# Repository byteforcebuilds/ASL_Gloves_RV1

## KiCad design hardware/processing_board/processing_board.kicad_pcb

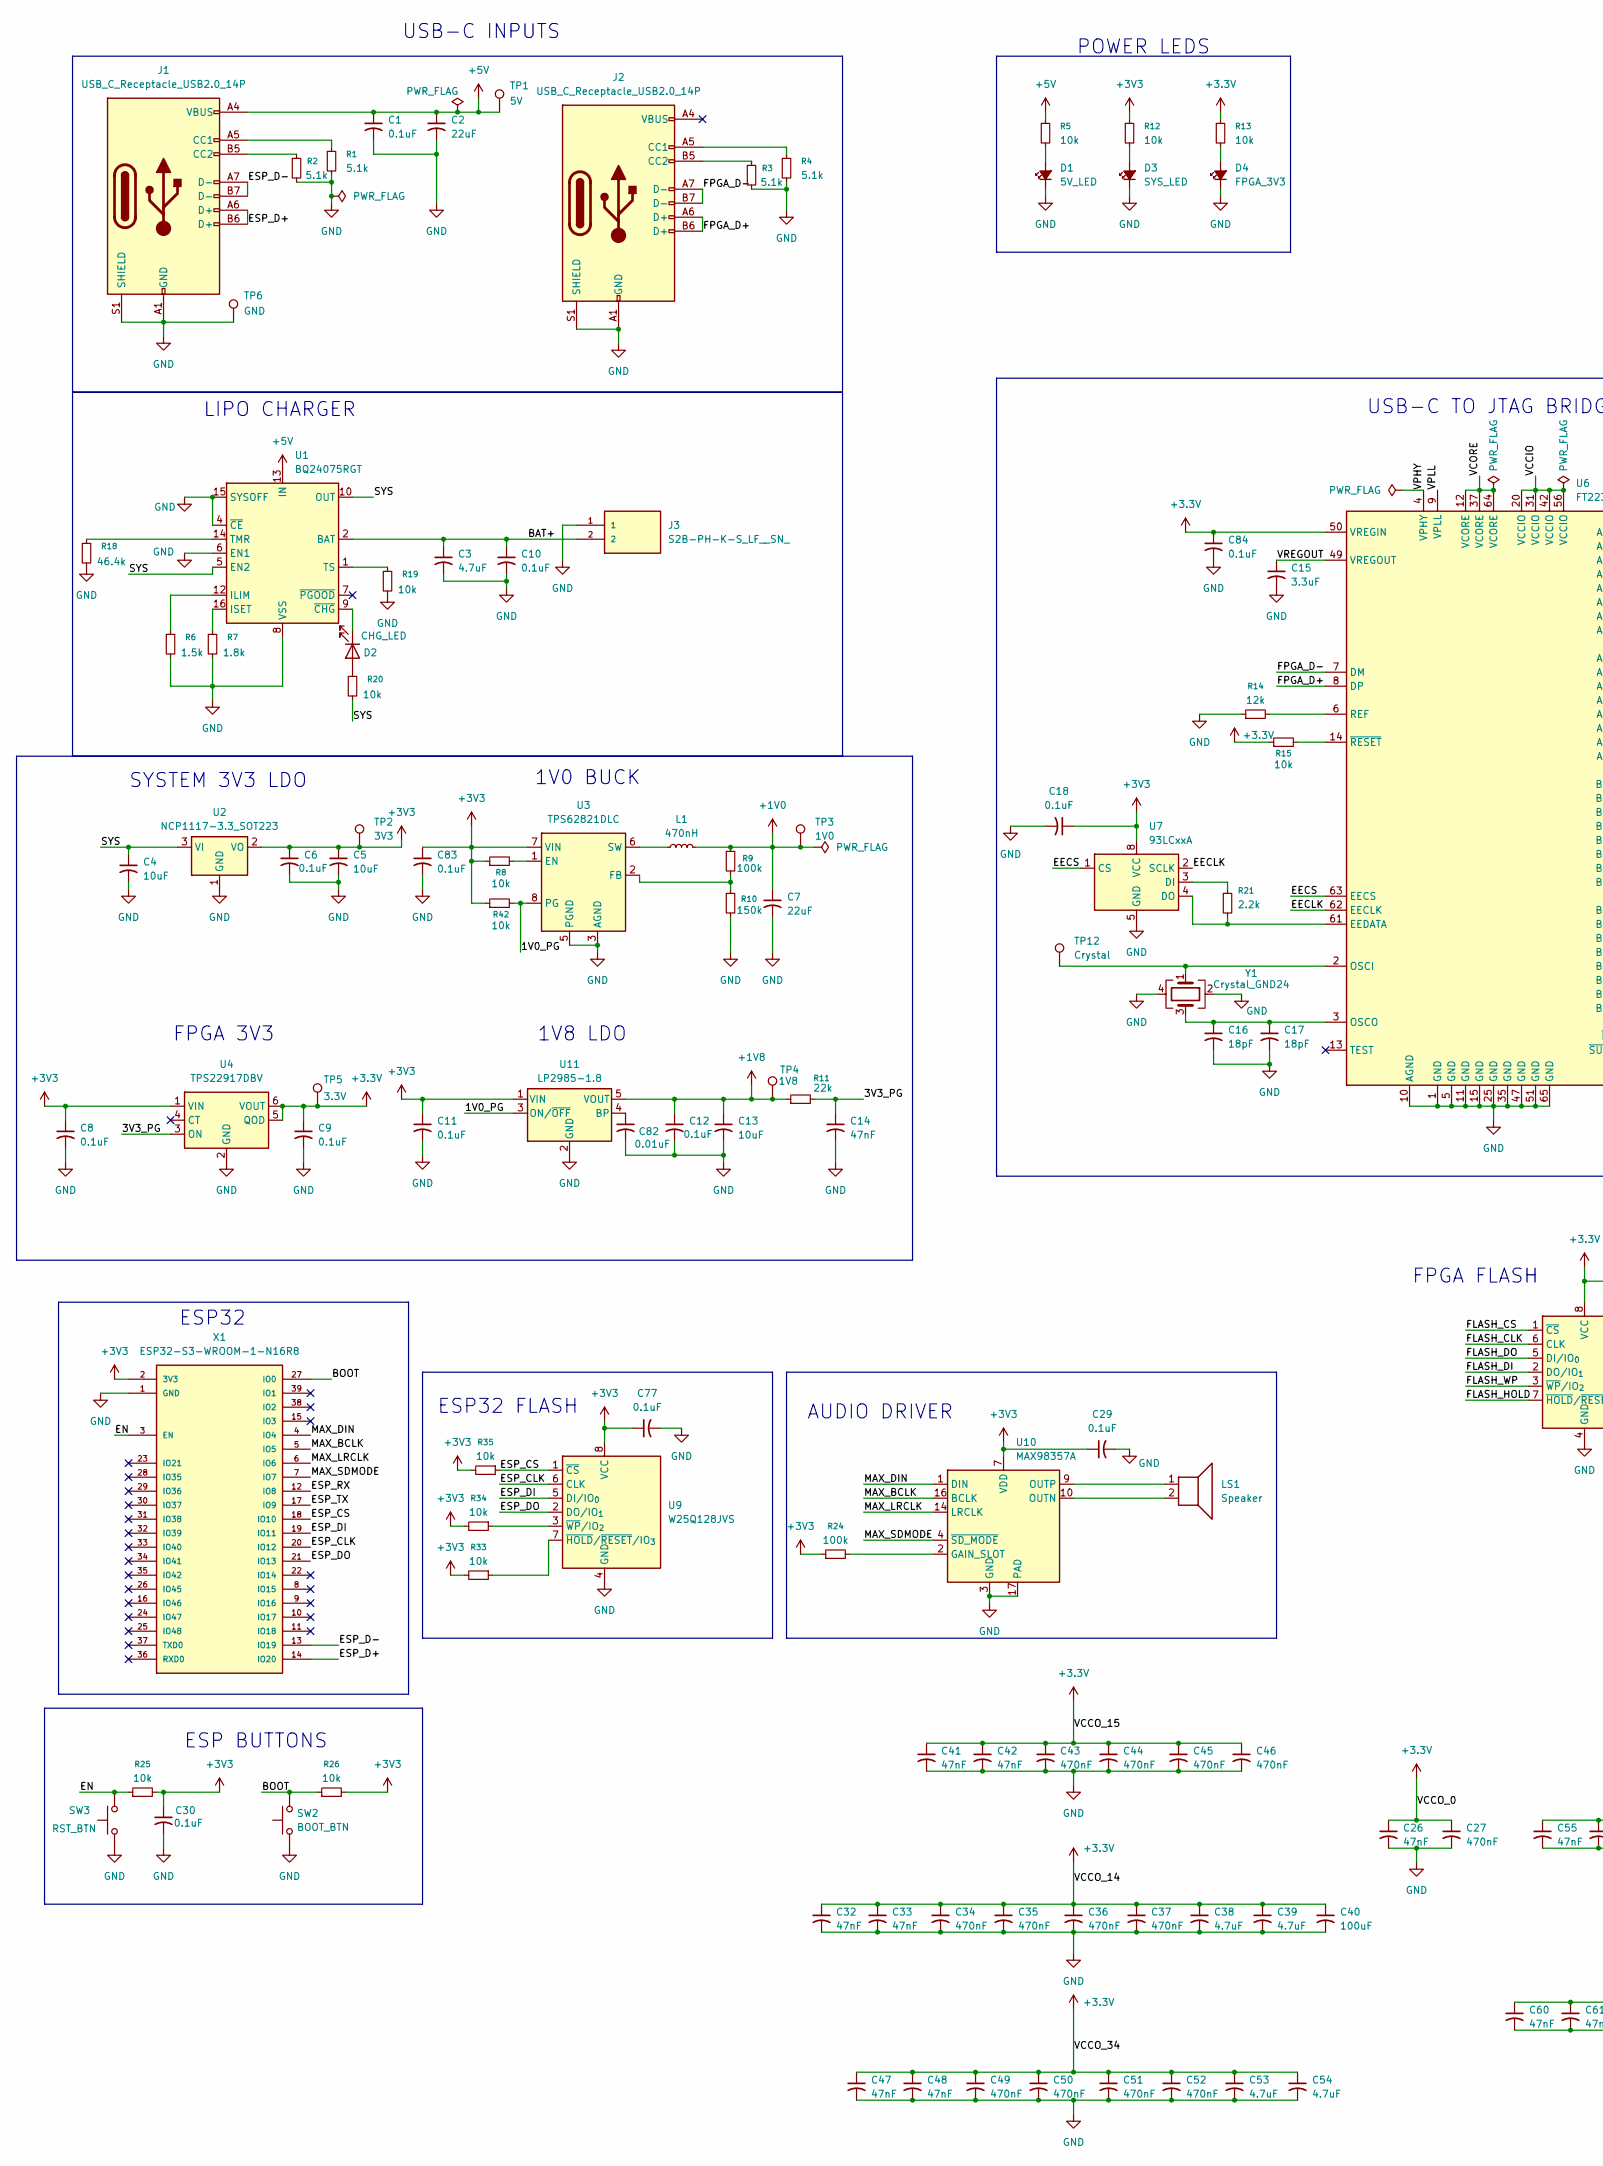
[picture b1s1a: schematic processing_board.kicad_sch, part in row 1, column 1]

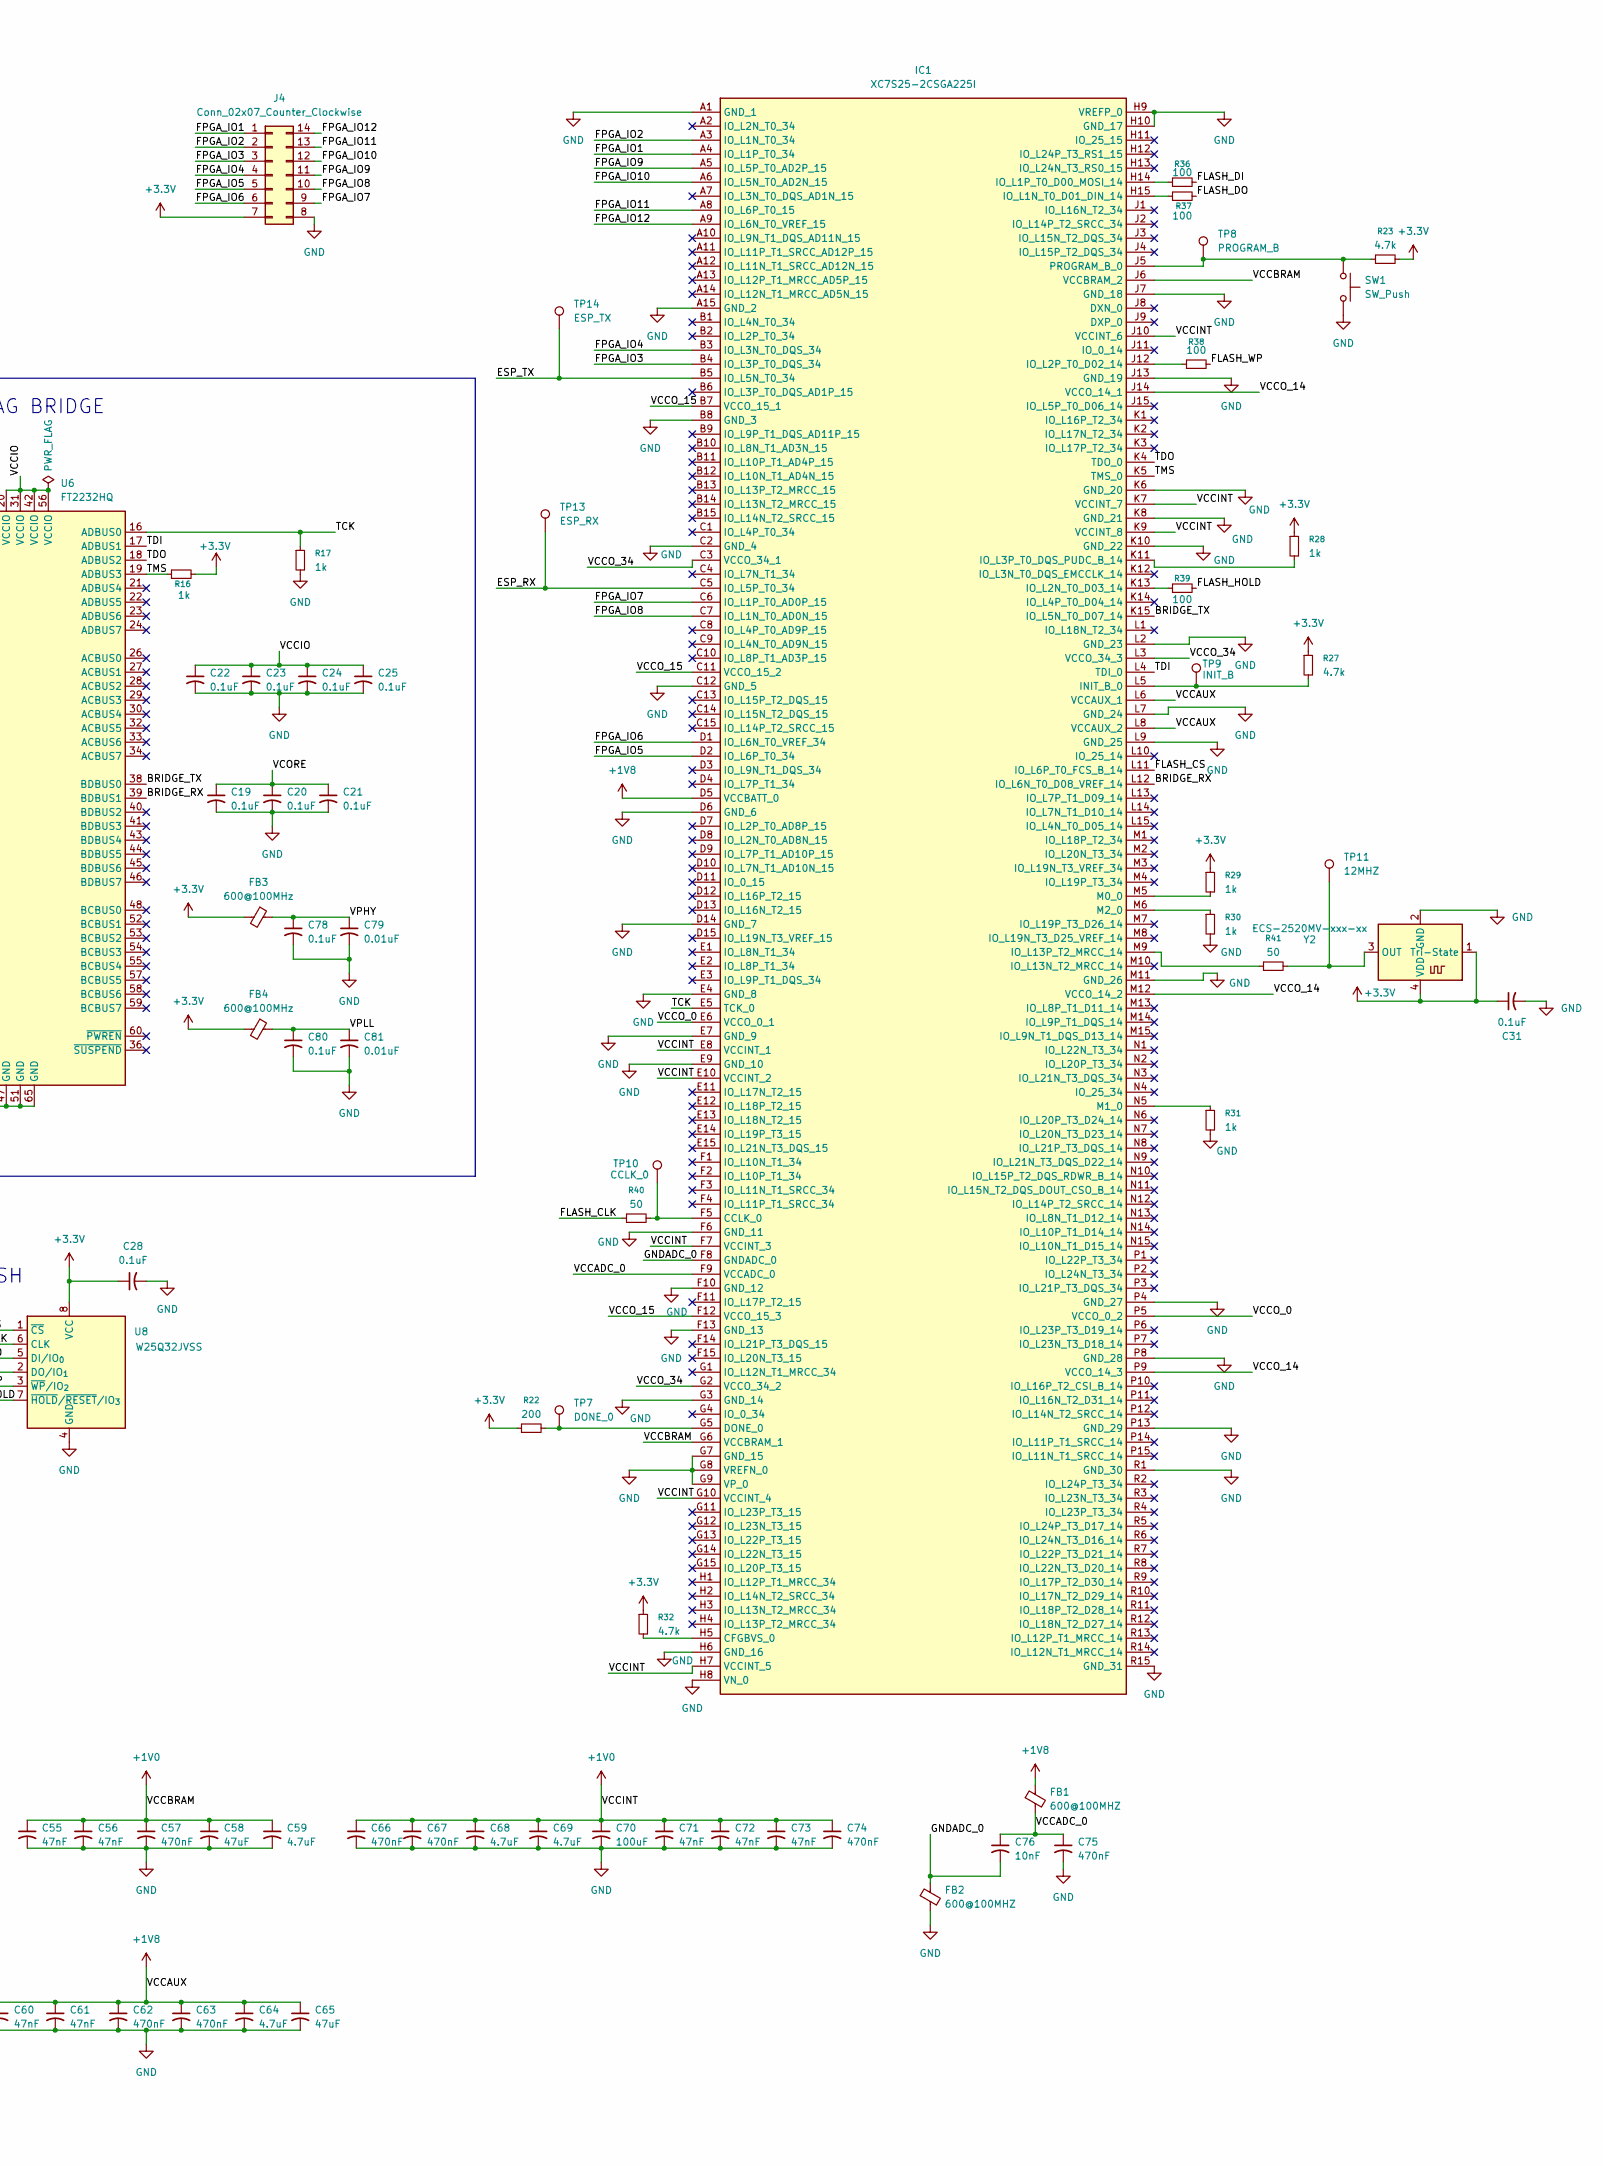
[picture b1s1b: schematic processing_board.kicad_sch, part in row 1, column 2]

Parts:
C1, C6, C8, C9, C11, C12, C18, C19, C20, C21, C22, C23, C24, C25, C28, C29, C30, C31, C77, C78, C80, C83, C84: 0.1uF; C_0402_1005Metric
C2, C7: 22uF; C_0805_2012Metric
C3, C38, C39, C53, C54, C59, C64, C68, C69: 4.7uF; C_0603_1608Metric
C4, C5, C13: 10uF; C_0805_2012Metric
C10: 0.1uF; R_0402_1005Metric
C14: 47nF; C_0805_2012Metric
C15: 3.3uF; C_0603_1608Metric
C16, C17: 18pF; C_0402_1005Metric
C26, C32, C33, C41, C42, C47, C48, C55, C56, C60, C61, C71, C72, C73: 47nF; C_0402_1005Metric
C27, C34, C35, C36, C37, C43, C44, C45, C46, C49, C50, C51, C52, C57, C62, C63, C66, C67, C74, C75: 470nF; C_0402_1005Metric
C40, C70: 100uF; C_0805_2012Metric
C58, C65: 47uF; C_0805_2012Metric
C76: 10nF; C_0402_1005Metric
C79, C81, C82: 0.01uF; C_0402_1005Metric
D1: 5V_LED; LED_0805_2012Metric
D2: CHG_LED; LED_0805_2012Metric
D3: SYS_LED; LED_0805_2012Metric
D4: FPGA_3V3; LED_0805_2012Metric
FB1, FB2: 600@100MHZ; C_0603_1608Metric
FB3, FB4: 600@100MHz; C_0603_1608Metric
IC1: XC7S25-2CSGA225I; BGA225C80P15X15_1300X1300X140; Manufacturer_Part_Number XC7S25-2CSGA225I; Mouser Part Number 217-XC7S25-2CSGA225I
J1, J2: USB_C_Receptacle_USB2.0_14P; USB_C_Receptacle_JAE_DX07S016JA1R1500
J3: S2B-PH-K-S_LF__SN_; JST_S2B-PH-K-S_LF__SN_
J4: Conn_02x07_Counter_Clockwise; PinHeader_2x07_P2.54mm_Vertical
L1: 470nH; INDC2016X120N
LS1: Speaker; JST_PH_S2B-PH-K_1x02_P2.00mm_Horizontal
R1, R2, R3, R4: 5.1k; R_0402_1005Metric
R5, R8, R12, R13, R15, R19, R20, R25, R26, R33, R34, R35, R42: 10k; R_0402_1005Metric
R6: 1.5k; R_0402_1005Metric
R7: 1.8k; R_0402_1005Metric
R9, R24: 100k; R_0402_1005Metric
R10: 150k; R_0402_1005Metric
R11: 22k; R_0402_1005Metric
R14: 12k; R_0402_1005Metric
R16, R17, R28, R29, R30, R31: 1k; R_0402_1005Metric
R18: 46.4k; R_0402_1005Metric
R21: 2.2k; R_0402_1005Metric
R22: 200; R_0402_1005Metric
R23, R27, R32: 4.7k; R_0402_1005Metric
R36, R37, R38, R39: 100; R_0402_1005Metric
R40, R41: 50; R_0402_1005Metric
SW1: SW_Push; SW_SPST_B3U-1000P
SW2: BOOT_BTN; SW_SPST_B3U-1000P
SW3: RST_BTN; SW_SPST_B3U-1000P
TP1: 5V; TestPoint_Loop_D2.60mm_Drill0.9mm_Beaded
TP2: 3V3; TestPoint_Loop_D2.60mm_Drill0.9mm_Beaded
TP3: 1V0; TestPoint_Loop_D2.60mm_Drill0.9mm_Beaded
TP4: 1V8; TestPoint_Loop_D2.60mm_Drill0.9mm_Beaded
TP5: 3.3V; TestPoint_Loop_D2.60mm_Drill0.9mm_Beaded
TP6: GND; TestPoint_Loop_D2.60mm_Drill0.9mm_Beaded
TP7: DONE_0; TestPoint_Loop_D2.60mm_Drill0.9mm_Beaded
TP8: PROGRAM_B; TestPoint_Loop_D2.60mm_Drill0.9mm_Beaded
TP9: INIT_B; TestPoint_Loop_D2.60mm_Drill0.9mm_Beaded
TP10: CCLK_0; TestPoint_Loop_D2.60mm_Drill0.9mm_Beaded
TP11: 12MHZ; TestPoint_Loop_D2.60mm_Drill0.9mm_Beaded
TP12: Crystal; TestPoint_Loop_D2.60mm_Drill0.9mm_Beaded
TP13: ESP_RX; TestPoint_Loop_D2.60mm_Drill0.9mm_Beaded
TP14: ESP_TX; TestPoint_Loop_D2.60mm_Drill0.9mm_Beaded
U1: BQ24075RGT; VQFN-16-1EP_3x3mm_P0.5mm_EP1.6x1.6mm
U2: NCP1117-3.3_SOT223; SOT-223-3_TabPin2
U3: TPS62821DLC; Texas_VSON-HR-8_1.5x2mm_P0.5mm
U4: TPS22917DBV; SOT-23-6
U6: FT2232HQ; QFN-64-1EP_9x9mm_P0.5mm_EP4.35x4.35mm
U7: 93LCxxA; SOIC-8_3.9x4.9mm_P1.27mm
U8: W25Q32JVSS; SOIC-8_5.3x5.3mm_P1.27mm
U9: W25Q128JVS; SOIC-8_5.3x5.3mm_P1.27mm
U10: MAX98357A; TQFN-16-1EP_3x3mm_P0.5mm_EP1.23x1.23mm
U11: LP2985-1.8; SOT-23-5
X1: ESP32-S3-WROOM-1-N16R8; ESP32S3WROOM1N8R2; MANUFACTURER_PART_NUMBER ESP32-S3-WROOM-1-N16R8
Y1: Crystal_GND24; Crystal_SMD_3225-4Pin_3.2x2.5mm
Y2: ECS-2520MV-xxx-xx; Oscillator_SMD_ECS_2520MV-xxx-xx-4Pin_2.5x2.0mm

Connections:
+1V0: C7.1, C55.1, C56.1, C57.1, C58.1, C59.1, C66.1, C67.1, C68.1, C69.1, C70.1, C71.1, C72.1, C73.1, C74.1, IC1.E8 (VCCINT_1), IC1.E10 (VCCINT_2), IC1.F7 (VCCINT_3), IC1.G6 (VCCBRAM_1), IC1.G10 (VCCINT_4), IC1.H7 (VCCINT_5), IC1.J6 (VCCBRAM_2), IC1.J10 (VCCINT_6), IC1.K7 (VCCINT_7), IC1.K9 (VCCINT_8), L1.2, R9.1, TP3.1
+1V8: C12.1, C13.1, C60.1, C61.1, C62.1, C63.1, C64.1, C65.1, FB1.1, IC1.D5 (VCCBATT_0), IC1.L6 (VCCAUX_1), IC1.L8 (VCCAUX_2), R11.1, TP4.1, U11.5 (VOUT)
+3.3V: C9.1, C26.1, C27.1, C28.1, C31.1, C32.1, C33.1, C34.1, C35.1, C36.1, C37.1, C38.1, C39.1, C40.1, C41.1, C42.1, C43.1, C44.1, C45.1, C46.1, C47.1, C48.1, C49.1, C50.1, C51.1, C52.1, C53.1, C54.1, C84.1, FB3.2, FB4.2, IC1.B7 (VCCO_15_1), IC1.C3 (VCCO_34_1), IC1.C11 (VCCO_15_2), IC1.E6 (VCCO_0_1), IC1.F12 (VCCO_15_3), IC1.G2 (VCCO_34_2), IC1.J14 (VCCO_14_1), IC1.L3 (VCCO_34_3), IC1.M12 (VCCO_14_2), IC1.P5 (VCCO_0_2), IC1.P9 (VCCO_14_3), J4.7, R13.1, R15.1, R16.2, R22.1, R23.2, R27.1, R28.1, R29.1, R32.1, TP5.1, U4.5 (QOD), U4.6 (VOUT), U6.50 (VREGIN), U8.8 (VCC), Y2.1 (Tri-State), Y2.4 (VDD)
+3V3: C5.1, C6.1, C8.1, C11.1, C18.1, C29.1, C30.1, C77.1, C83.1, R8.1, R12.1, R24.1, R25.2, R26.2, R33.2, R34.2, R35.2, R42.1, TP2.1, U2.2 (VO), U3.7 (VIN), U4.1 (VIN), U7.8 (VCC), U9.8 (VCC), U10.7 (VDD), U10.8 (VDD), U11.1 (VIN), X1.2 (3V3)
+5V: C1.1, C2.1, J1.A4 (VBUS), J1.A9 (VBUS), J1.B4 (VBUS), J1.B9 (VBUS), R5.1, TP1.1, U1.13 (IN)
/1V0_PG: R42.2, U3.8 (PG), U11.3 (ON/~OFF)
/3V3_PG: C14.1, R11.2, U4.3 (ON)
/<NO NET>: C3.1, C10.1, J3.2, U1.2 (BAT), U1.3 (BAT)
/BOOT: R26.1, SW2.2, X1.27 (IO0)
/BRIDGE_RX: IC1.L12 (IO_L6N_T0_D08_VREF_14), U6.39 (BDBUS1)
/BRIDGE_TX: IC1.K15 (IO_L5N_T0_D07_14), U6.38 (BDBUS0)
/EECLK: U6.62 (EECLK), U7.2 (SCLK)
/EECS: U6.63 (EECS), U7.1 (CS)
/EN: R25.1, SW3.2, X1.3 (EN)
/ESP_CLK: U9.6 (CLK), X1.20 (IO12)
/ESP_CS: R35.1, U9.1 (~CS), X1.18 (IO10)
/ESP_D+: J1.A6 (D+), J1.B6 (D+), X1.14 (IO20)
/ESP_D-: J1.A7 (D-), J1.B7 (D-), X1.13 (IO19)
/ESP_DI: U9.5 (DI/IO_{0}), X1.19 (IO11)
/ESP_DO: U9.2 (DO/IO_{1}), X1.21 (IO13)
/ESP_RX: IC1.C5 (IO_L5P_T0_34), TP13.1, X1.12 (IO8)
/ESP_TX: IC1.B5 (IO_L5N_T0_34), TP14.1, X1.17 (IO9)
/FLASH_CLK: R40.1, U8.6 (CLK)
/FLASH_CS: IC1.L11 (IO_L6P_T0_FCS_B_14), U8.1 (~CS)
/FLASH_DI: R36.2, U8.2 (DO/IO_{1})
/FLASH_DO: R37.2, U8.5 (DI/IO_{0})
/FLASH_HOLD: R39.2, U8.7 (~HOLD/~RESET/IO_{3})
/FLASH_WP: R38.2, U8.3 (~WP/IO_{2})
/FPGA_D+: J2.A6 (D+), J2.B6 (D+), U6.8 (DP)
/FPGA_D-: J2.A7 (D-), J2.B7 (D-), U6.7 (DM)
/FPGA_IO1: IC1.A4 (IO_L1P_T0_34), J4.1
/FPGA_IO2: IC1.A3 (IO_L1N_T0_34), J4.2
/FPGA_IO3: IC1.B4 (IO_L3P_T0_DQS_34), J4.3
/FPGA_IO4: IC1.B3 (IO_L3N_T0_DQS_34), J4.4
/FPGA_IO5: IC1.D2 (IO_L6P_T0_34), J4.5
/FPGA_IO6: IC1.D1 (IO_L6N_T0_VREF_34), J4.6
/FPGA_IO7: IC1.C6 (IO_L1P_T0_AD0P_15), J4.9
/FPGA_IO8: IC1.C7 (IO_L1N_T0_AD0N_15), J4.10
/FPGA_IO9: IC1.A5 (IO_L5P_T0_AD2P_15), J4.11
/FPGA_IO10: IC1.A6 (IO_L5N_T0_AD2N_15), J4.12
/FPGA_IO11: IC1.A8 (IO_L6P_T0_15), J4.13
/FPGA_IO12: IC1.A9 (IO_L6N_T0_VREF_15), J4.14
/GNDADC_0: C76.2, FB2.1, IC1.F8 (GNDADC_0)
/MAX_BCLK: U10.16 (BCLK), X1.5 (IO5)
/MAX_DIN: U10.1 (DIN), X1.4 (IO4)
/MAX_LRCLK: U10.14 (LRCLK), X1.6 (IO6)
/MAX_SDMODE: U10.4 (~SD_MODE), X1.7 (IO7)
/SYS: C4.1, R20.2, U1.5 (EN2), U1.10 (OUT), U1.11 (OUT), U2.3 (VI)
/TCK: IC1.E5 (TCK_0), R17.1, U6.16 (ADBUS0)
/TDI: IC1.L4 (TDI_0), U6.17 (ADBUS1)
/TDO: IC1.K4 (TDO_0), U6.18 (ADBUS2)
/TMS: IC1.K5 (TMS_0), R16.1, U6.19 (ADBUS3)
/VCCADC_0: C75.1, C76.1, FB1.2, IC1.F9 (VCCADC_0)
/VCCIO: C22.1, C23.1, C24.1, C25.1, U6.20 (VCCIO), U6.31 (VCCIO), U6.42 (VCCIO), U6.56 (VCCIO)
/VCORE: C19.1, C20.1, C21.1, U6.12 (VCORE), U6.37 (VCORE), U6.64 (VCORE)
/VPHY: C78.1, C79.1, FB3.1, U6.4 (VPHY)
/VPLL: C80.1, C81.1, FB4.1, U6.9 (VPLL)
/VREGOUT: C15.1, U6.49 (VREGOUT)
GND: C1.2, C2.2, C3.2, C4.2, C5.2, C6.2, C7.2, C8.2, C9.2, C10.2, C11.2, C12.2, C13.2, C14.2, C15.2, C16.2, C17.2, C18.2, C19.2, C20.2, C21.2, C22.2, C23.2, C24.2, C25.2, C26.2, C27.2, C28.2, C29.2, C30.2, C31.2, C32.2, C33.2, C34.2, C35.2, C36.2, C37.2, C38.2, C39.2, C40.2, C41.2, C42.2, C43.2, C44.2, C45.2, C46.2, C47.2, C48.2, C49.2, C50.2, C51.2, C52.2, C53.2, C54.2, C55.2, C56.2, C57.2, C58.2, C59.2, C60.2, C61.2, C62.2, C63.2, C64.2, C65.2, C66.2, C67.2, C68.2, C69.2, C70.2, C71.2, C72.2, C73.2, C74.2, C75.2, C77.2, C78.2, C79.2, C80.2, C81.2, C82.2, C83.2, C84.2, D1.1 (K), D3.1 (K), D4.1 (K), FB2.2, IC1.A1 (GND_1), IC1.A15 (GND_2), IC1.B8 (GND_3), IC1.C2 (GND_4), IC1.C12 (GND_5), IC1.D6 (GND_6), IC1.D14 (GND_7), IC1.E4 (GND_8), IC1.E7 (GND_9), IC1.E9 (GND_10), IC1.F6 (GND_11), IC1.F10 (GND_12), IC1.F13 (GND_13), IC1.G3 (GND_14), IC1.G7 (GND_15), IC1.G8 (VREFN_0), IC1.G9 (VP_0), IC1.H6 (GND_16), IC1.H8 (VN_0), IC1.H9 (VREFP_0), IC1.H10 (GND_17), IC1.J7 (GND_18), IC1.J13 (GND_19), IC1.K6 (GND_20), IC1.K8 (GND_21), IC1.K10 (GND_22), IC1.L2 (GND_23), IC1.L7 (GND_24), IC1.L9 (GND_25), IC1.M11 (GND_26), IC1.P4 (GND_27), IC1.P8 (GND_28), IC1.P13 (GND_29), IC1.R1 (GND_30), IC1.R15 (GND_31), J1.A1 (GND), J1.A12 (GND), J1.B1 (GND), J1.B12 (GND), J1.S1 (SHIELD), J2.A1 (GND), J2.A12 (GND), J2.B1 (GND), J2.B12 (GND), J2.S1 (SHIELD), J3.1, J4.8, R1.2, R2.2, R3.2, R4.2, R6.2, R7.2, R10.2, R14.1, R17.2, R18.2, R19.2, R30.2, R31.2, SW1.2, SW2.1, SW3.1, TP6.1, U1.4 (~CE), U1.6 (EN1), U1.8 (VSS), U1.15 (SYSOFF), U1.17 (VSS), U2.1 (GND), U3.3 (AGND), U3.5 (PGND), U4.2 (GND), U6.1 (GND), U6.5 (GND), U6.10 (AGND), U6.11 (GND), U6.15 (GND), U6.25 (GND), U6.35 (GND), U6.47 (GND), U6.51 (GND), U6.65 (GND), U7.5 (GND), U8.4 (GND), U9.4 (GND), U10.3 (GND), U10.11 (GND), U10.15 (GND), U10.17 (PAD), U11.2 (GND), X1.1 (GND), X1.40 (GND), X1.41 (GND), X1.42 (GND), X1.43 (GND), X1.44 (GND), X1.45 (GND), X1.46 (GND), X1.47 (GND), X1.48 (GND), X1.49 (GND), Y1.2, Y1.4, Y2.2 (GND)
unnamed: D1.2 (A), R5.2
unnamed: D2.2 (A), R20.1
unnamed: D2.1 (K), U1.9 (~CHG)
unnamed: D3.2 (A), R12.2
unnamed: D4.2 (A), R13.2
unnamed: IC1.F5 (CCLK_0), R40.2, TP10.1
unnamed: IC1.H5 (CFGBVS_0), R32.2
unnamed: IC1.G5 (DONE_0), R22.2, TP7.1
unnamed: IC1.L5 (INIT_B_0), R27.2, TP9.1
unnamed: IC1.H15 (IO_L1N_T0_D01_DIN_14), R37.1
unnamed: IC1.H14 (IO_L1P_T0_D00_MOSI_14), R36.1
unnamed: IC1.K13 (IO_L2N_T0_D03_14), R39.1
unnamed: IC1.J12 (IO_L2P_T0_D02_14), R38.1
unnamed: IC1.K11 (IO_L3P_T0_DQS_PUDC_B_14), R28.2
unnamed: IC1.M9 (IO_L13P_T2_MRCC_14), R41.1
unnamed: IC1.M5 (M0_0), R29.2
unnamed: IC1.N5 (M1_0), R31.1
unnamed: IC1.M6 (M2_0), R30.1
unnamed: IC1.J5 (PROGRAM_B_0), R23.1, SW1.1, TP8.1
unnamed: J1.A5 (CC1), R1.1
unnamed: J1.B5 (CC2), R2.1
unnamed: J2.A5 (CC1), R4.1
unnamed: J2.B5 (CC2), R3.1
unnamed: R6.1, U1.12 (ILIM)
unnamed: R7.1, U1.16 (ISET)
unnamed: R18.1, U1.14 (TMR)
unnamed: R19.1, U1.1 (TS)
unnamed: R8.2, U3.1 (EN)
unnamed: R9.2, R10.1, U3.2 (FB)
unnamed: L1.1, U3.6 (SW)
unnamed: R21.2, U6.61 (EEDATA), U7.4 (DO)
unnamed: TP12.1, U6.2 (OSCI), Y1.1
unnamed: C16.1, C17.1, U6.3 (OSCO), Y1.3
unnamed: R14.2, U6.6 (REF)
unnamed: R15.2, U6.14 (~RESET)
unnamed: R21.1, U7.3 (DI)
unnamed: R33.1, U9.7 (~HOLD/~RESET/IO_{3})
unnamed: R34.1, U9.3 (~WP/IO_{2})
unnamed: R24.2, U10.2 (GAIN_SLOT)
unnamed: C82.1, U11.4 (BP)
unnamed: R41.2, TP11.1, Y2.3 (OUT)

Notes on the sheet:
1V0 BUCK
ESP BUTTONS
LIPO CHARGER
SYSTEM 3V3 LDO
FPGA FLASH
POWER LEDS
FPGA 3V3
USB-C INPUTS
1V8 LDO
USB-C TO JTAG BRIDGE
AUDIO DRIVER
ESP32
ESP32 FLASH

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
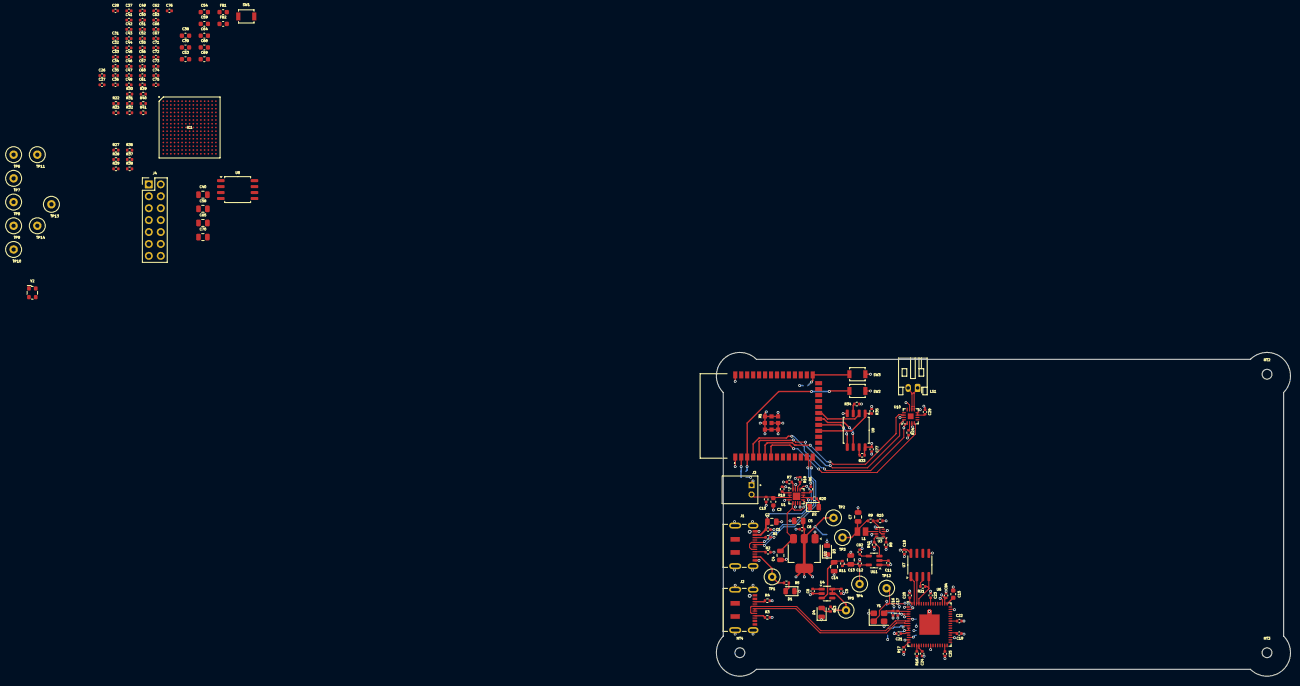
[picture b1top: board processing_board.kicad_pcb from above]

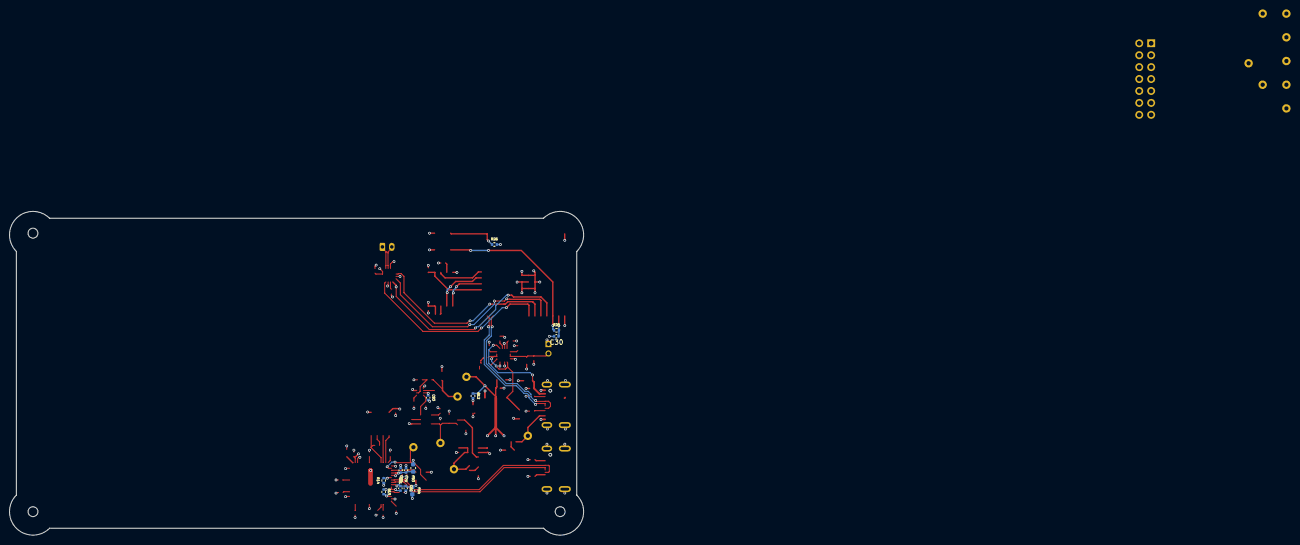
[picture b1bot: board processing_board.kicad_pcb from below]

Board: 4 copper layers, 122.3 x 69.0 mm, 174 parts (13 on the bottom side), 100 nets.

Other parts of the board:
MT2, MT3, MT4: MountingHole_2.1mm

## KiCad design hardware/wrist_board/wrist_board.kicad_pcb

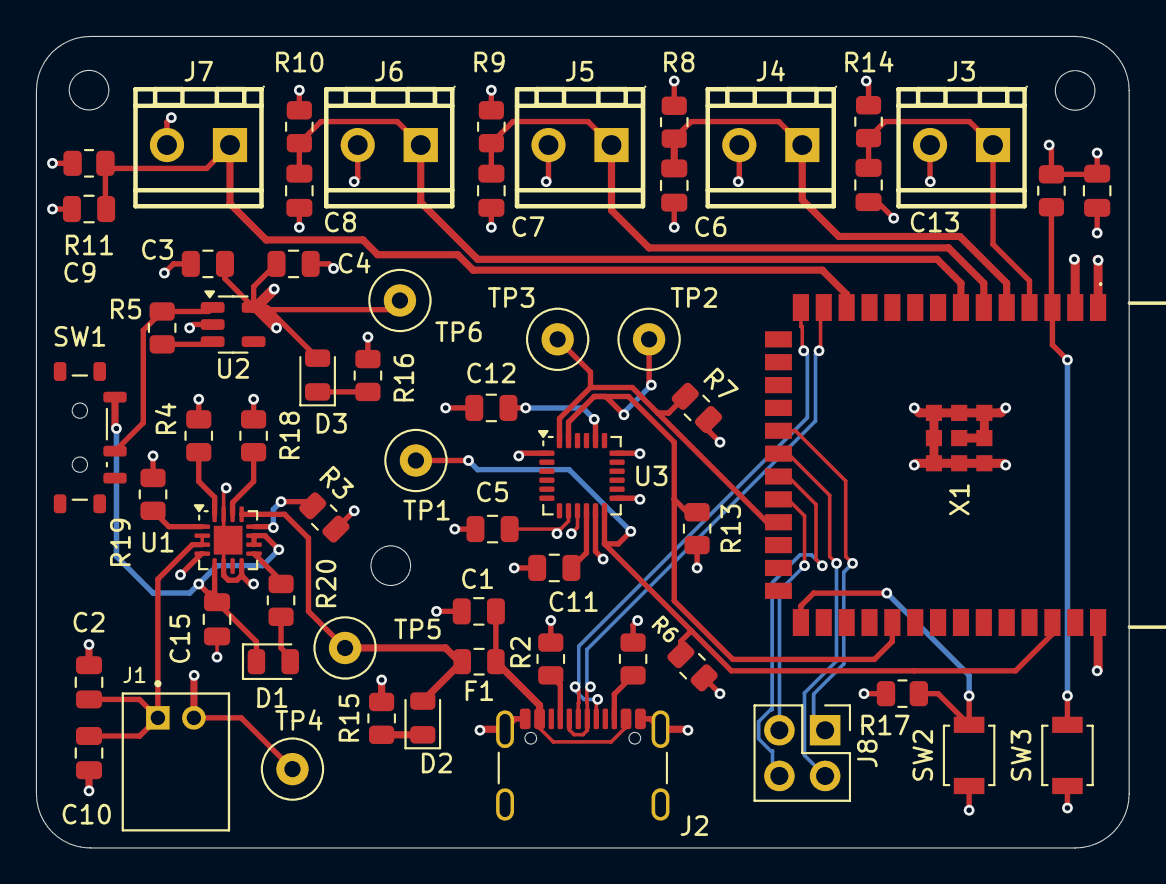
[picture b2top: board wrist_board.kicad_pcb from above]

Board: 4 copper layers, 60.7 x 45.1 mm, 60 parts (0 on the bottom side), 36 nets.

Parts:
C1, C3, C15: 10uF; C_0805_2012Metric
C2: 4.7uF; C_0805_2012Metric
C4, C5, C6, C7, C8, C9, C10, C11, C13, C14: 0.1uF; C_0805_2012Metric
C12: 2.2nF; C_0805_2012Metric
D1: CHG_LED; LED_0805_2012Metric
D2: 5V_LED; LED_0805_2012Metric
D3: 3V3_LED; LED_0805_2012Metric
F1: Polyfuse; Fuse_0805_2012Metric
J1: S2B-PH-K-S_LF__SN_; JST_S2B-PH-K-S_LF__SN_
J2: USB_C_Receptacle_USB2.0_14P; USB_C_Receptacle_GCT_USB4105-xx-A_16P_TopMnt_Horizontal
J3, J4, J5, J6, J7: Conn_01x02; CONN-TH_DG350-3.5-02P-14-00A-H
J8: GPIOs; PinHeader_2x02_P2.54mm_Vertical
R1, R2: 5.1k; R_0805_2012Metric
R3: 1.5k; R_0805_2012Metric
R4: 1.8k; R_0805_2012Metric
R5, R12, R17, R19: 10k; R_0805_2012Metric
R6, R7, R13: 4.7k; R_0805_2012Metric
R8, R9, R10, R11, R14: 22k; R_0805_2012Metric
R15, R16, R20: 1k; R_0805_2012Metric
R18: 46.4k; R_0805_2012Metric
SW1: SW_SPST; SW_SPDT_Shouhan_MSK12C02
SW2: BOOT_BTN; SW_SPST_B3U-1000P
SW3: RST_BTN; SW_SPST_B3U-1000P
TP1: INT_TP; TestPoint_Loop_D2.60mm_Drill0.9mm_Beaded
TP2: SCL_TP; TestPoint_Loop_D2.60mm_Drill0.9mm_Beaded
TP3: SDA_TP; TestPoint_Loop_D2.60mm_Drill0.9mm_Beaded
TP4: GND_TP; TestPoint_Loop_D2.60mm_Drill0.9mm_Beaded
TP5: 5V_TP; TestPoint_Loop_D2.60mm_Drill0.9mm_Beaded
TP6: 3V3_TP; TestPoint_Loop_D2.60mm_Drill0.9mm_Beaded
U1: BQ24075RGT; VQFN-16-1EP_3x3mm_P0.5mm_EP1.6x1.6mm
U2: TLV75533PDBV; SOT-23-5
U3: MPU-6050; InvenSense_QFN-24_4x4mm_P0.5mm
X1: ESP32-S3-WROOM-1-N16R8; ESP32S3WROOM1N8R2

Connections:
+3V3: C3.1, C4.1, C5.1, C14.1, D3.2 (A), R6.1, R7.1, R8.2, R9.2, R10.2, R11.2, R12.2, R13.1, R14.2, R17.2, TP6.1, U2.5 (OUT), U3.8 (VLOGIC), U3.13 (VDD), X1.2 (3V3)
+5V: D2.2 (A), F1.2, TP5.1, U1.13 (IN)
/<NO NET>: C2.1, C10.1, J1.1, U1.2 (BAT), U1.3 (BAT)
/BOOT: R17.1, SW2.2, X1.27 (IO0)
/D+: J2.A6 (D+), J2.B6 (D+), X1.14 (IO20)
/D-: J2.A7 (D-), J2.B7 (D-), X1.13 (IO19)
/EN: R12.1, SW3.2, X1.3 (EN)
/FS_1: C13.1, J3.1, R14.1, X1.4 (IO4)
/FS_2: C6.1, J4.1, R8.1, X1.5 (IO5)
/FS_3: C7.1, J5.1, R9.1, X1.6 (IO6)
/FS_4: C8.1, J6.1, R10.1, X1.7 (IO7)
/FS_5: C9.1, J7.1, R11.1, X1.12 (IO8)
/INT: R6.2, TP1.1, U3.12 (INT), X1.38 (IO2)
/IO11: J8.1, X1.19 (IO11)
/IO12: J8.2, X1.20 (IO12)
/IO13: J8.4, X1.21 (IO13)
/IO14: J8.3, X1.22 (IO14)
/SCL: R13.2, TP2.1, U3.23 (SCL), X1.31 (IO38)
/SDA: R7.2, TP3.1, U3.24 (SDA), X1.23 (IO21)
/SYS: C15.1, R20.2, SW1.1 (A), U1.5 (EN2), U1.10 (OUT), U1.11 (OUT)
GND: C1.2, C2.2, C3.2, C4.2, C5.2, C6.2, C7.2, C8.2, C9.2, C10.2, C11.2, C12.2, C13.2, C14.2, C15.2, J1.2, J2.A1 (GND), J2.A12 (GND), J2.B1 (GND), J2.B12 (GND), J2.S1 (SHIELD), J3.2, J4.2, J5.2, J6.2, J7.2, R1.2, R2.2, R3.2, R4.2, R15.2, R16.2, R18.2, R19.2, SW2.1, SW3.1, TP4.1, U1.4 (~CE), U1.6 (EN1), U1.8 (VSS), U1.15 (SYSOFF), U1.17 (VSS), U2.2 (GND), U3.1 (CLKIN), U3.9 (AD0), U3.11 (FSYNC), U3.18 (GND), X1.1 (GND), X1.40 (GND), X1.41 (GND), X1.42 (GND), X1.43 (GND), X1.44 (GND), X1.45 (GND), X1.46 (GND), X1.47 (GND), X1.48 (GND), X1.49 (GND)
unnamed: C1.1, F1.1, J2.A4 (VBUS), J2.A9 (VBUS), J2.B4 (VBUS), J2.B9 (VBUS)
unnamed: D1.2 (A), R20.1
unnamed: D1.1 (K), U1.9 (~CHG)
unnamed: D2.1 (K), R15.1
unnamed: D3.1 (K), R16.1
unnamed: J2.A5 (CC1), R2.1
unnamed: J2.B5 (CC2), R1.1
unnamed: R5.1, SW1.2 (B), U2.1 (IN)
unnamed: R3.1, U1.12 (ILIM)
unnamed: R4.1, U1.16 (ISET)
unnamed: R18.1, U1.14 (TMR)
unnamed: R19.1, U1.1 (TS)
unnamed: R5.2, U2.3 (EN)
unnamed: C12.1, U3.20 (CPOUT)
unnamed: C11.1, U3.10 (REGOUT)

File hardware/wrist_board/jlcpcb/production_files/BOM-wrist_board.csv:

Comment,Designator,Footprint,LCSC,Quantity
0.1uF,"C10,C11,C12,C13,C14,C4,C5,C6,C7,C8,C9",C_0805_2012Metric,C49678,11
1.5k,R3,R_0805_2012Metric,C4310,1
1.8k,R4,R_0805_2012Metric,C17398,1
10k,"R12,R17,R19,R5",R_0805_2012Metric,C17414,4
10uF,"C1,C15,C3",C_0805_2012Metric,C1713,3
1k,"R15,R16,R20",R_0805_2012Metric,C17513,3
22k,"R10,R11,R14,R8,R9",R_0805_2012Metric,C17560,5
3V3_LED,D3,LED_0805_2012Metric,C2297,1
3V3_TP,TP6,TestPoint_Loop_D2.60mm_Drill0.9mm_Beaded,C238122,1
4.7k,"R13,R6,R7",R_0805_2012Metric,C17673,3
4.7uF,C2,C_0805_2012Metric,C1779,1
46.4k,R18,R_0805_2012Metric,C17713,1
5.1k,"R1,R2",R_0805_2012Metric,C27834,2
5V_LED,D2,LED_0805_2012Metric,C2297,1
5V_TP,TP5,TestPoint_Loop_D2.60mm_Drill0.9mm_Beaded,C238122,1
BOOT_BTN,SW2,SW_SPST_B3U-1000P,C231329,1
BQ24075RGT,U1,VQFN-16-1EP_3x3mm_P0.5mm_EP1.6x1.6mm,C15464,1
CHG_LED,D1,LED_0805_2012Metric,C2297,1
Conn_01x02,"J3,J4,J5,J6,J7",CONN-TH_DG350-3.5-02P-14-00A-H,C2760668,5
ESP32-S3-WROOM-1-N16R8,X1,ESP32S3WROOM1N8R2,C2913202,1
GND_TP,TP4,TestPoint_Loop_D2.60mm_Drill0.9mm_Beaded,C238122,1
GPIOs,J8,PinHeader_2x02_P2.54mm_Vertical,C492419,1
INT_TP,TP1,TestPoint_Loop_D2.60mm_Drill0.9mm_Beaded,C238122,1
MPU-6050,U3,InvenSense_QFN-24_4x4mm_P0.5mm,C24112,1
Polyfuse,F1,Fuse_0805_2012Metric,C181350,1
RST_BTN,SW3,SW_SPST_B3U-1000P,C231329,1
S2B-PH-K-S_LF__SN_,J1,JST_S2B-PH-K-S_LF__SN_,C173752,1
SCL_TP,TP2,TestPoint_Loop_D2.60mm_Drill0.9mm_Beaded,C238122,1
SDA_TP,TP3,TestPoint_Loop_D2.60mm_Drill0.9mm_Beaded,C238122,1
SW_SPST,SW1,SW_SPDT_Shouhan_MSK12C02,C431540,1
TLV75533PDBV,U2,SOT-23-5,C404027,1
USB_C_Receptacle_USB2.0_14P,J2,USB_C_Receptacle_GCT_USB4105-xx-A_16P_TopMnt_Horizontal,C2988369,1

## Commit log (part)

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2026-05-15 Added wrist board project files
2026-05-21 Basic power circuitry added
2026-05-21 Minor updates to charging circuit
2026-05-21 Added hierarchical pages and 3v3 circuitry
2026-05-21 Added flex sensor circuitry and ESP
2026-05-21 MPU 6050 IMU circuitry added
2026-05-21 Added LEDs and power switch to power schematic
2026-05-23 USB C 2.0 receptacle updated
2026-05-23 Added male 2.54mm headers for flex sensor connection
2026-05-23 Minor updates to both power and esp schematics
2026-05-23 All prototype footprints assigned
2026-05-23 Schematics condensed into one, labels added
2026-05-23 layout started
2026-05-25 New board orientation + USB/PWR routing
2026-05-25 3v3 PWR + flex sensor header routing
2026-05-25 updated analysis with mutual 4791 goals and action plan
2026-05-25 Added SDA and SCL routing/pullups
2026-05-25 Added voltage divider resistors for flex sensors
2026-05-25 All major components routed, still needs extra GPIO pinouts
2026-05-25 Added boot and reset buttons in schematic
2026-05-25 Added extra GPIO pinout
2026-05-25 Added test points to layout
2026-05-25 Test points and extra GPIOs added to layout
2026-05-25 Minor changes to pass DRC
2026-05-25 Updated silkscreen and fills
2026-05-25 folder schema and inital viso drawings
2026-05-25 visio update
2026-05-26 docker setup
2026-05-26 updating requirements and initial data exploration notebook
2026-05-26 beautiful graphs analyzing figshare dataset for initial and markdown file synthesizing analytical findings
2026-05-29 Updates to wrist board for horizontal connections + mounting holes
2026-05-30 gowin project setup
2026-06-01 Added all JLC part numbers + generated production files
2026-06-03 md files
2026-06-03 implement ASL dataset pipeline with abstract base class and static/dynamic subclasses
2026-06-03 Replaced old charging circuit, allows for input power derived from USB C or LIPO
2026-06-03 gowin automation
2026-06-03 docker for gowin
2026-06-03 Replaced dupont headers with screw terminal
2026-06-05 updating notebook to export all figures
2026-06-16 amd toolchain setup
2026-06-16 reverted docker
2026-06-19 Created processing board proj files, added usb c connectors
2026-06-19 Added 3v3 LDO and 1V0 buck
2026-06-19 Full power tree added
2026-06-19 Added JTAG to USB C bridge
2026-06-22 nerual net notebooks
2026-06-22 updated graphics for presentation and report
2026-06-23 Added FPGA bypass caps
2026-06-24 Schematic is a disaster, passes ERC
2026-06-24 Added all footprints
2026-06-24 Created netlist and imported it to the PCB editor
2026-06-24 Routed charging circuit
2026-06-24 Added 1V0 buck circuit
2026-06-24 Added 1V8 LDO circuit
2026-06-24 Added 3.3V FPGA rail LDO
2026-06-24 Added BOOT and RST btns for ESP32, routed flash
2026-06-24 Routed audio amplifier and speaker jack
2026-06-25 Added routed USB-C to JTAG bridge
2026-06-29 file schema updated for FPGA and MCU
